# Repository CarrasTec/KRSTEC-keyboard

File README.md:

# KRSTEC-keyboard

These are the KiCad Files for the keyboard that I designed.

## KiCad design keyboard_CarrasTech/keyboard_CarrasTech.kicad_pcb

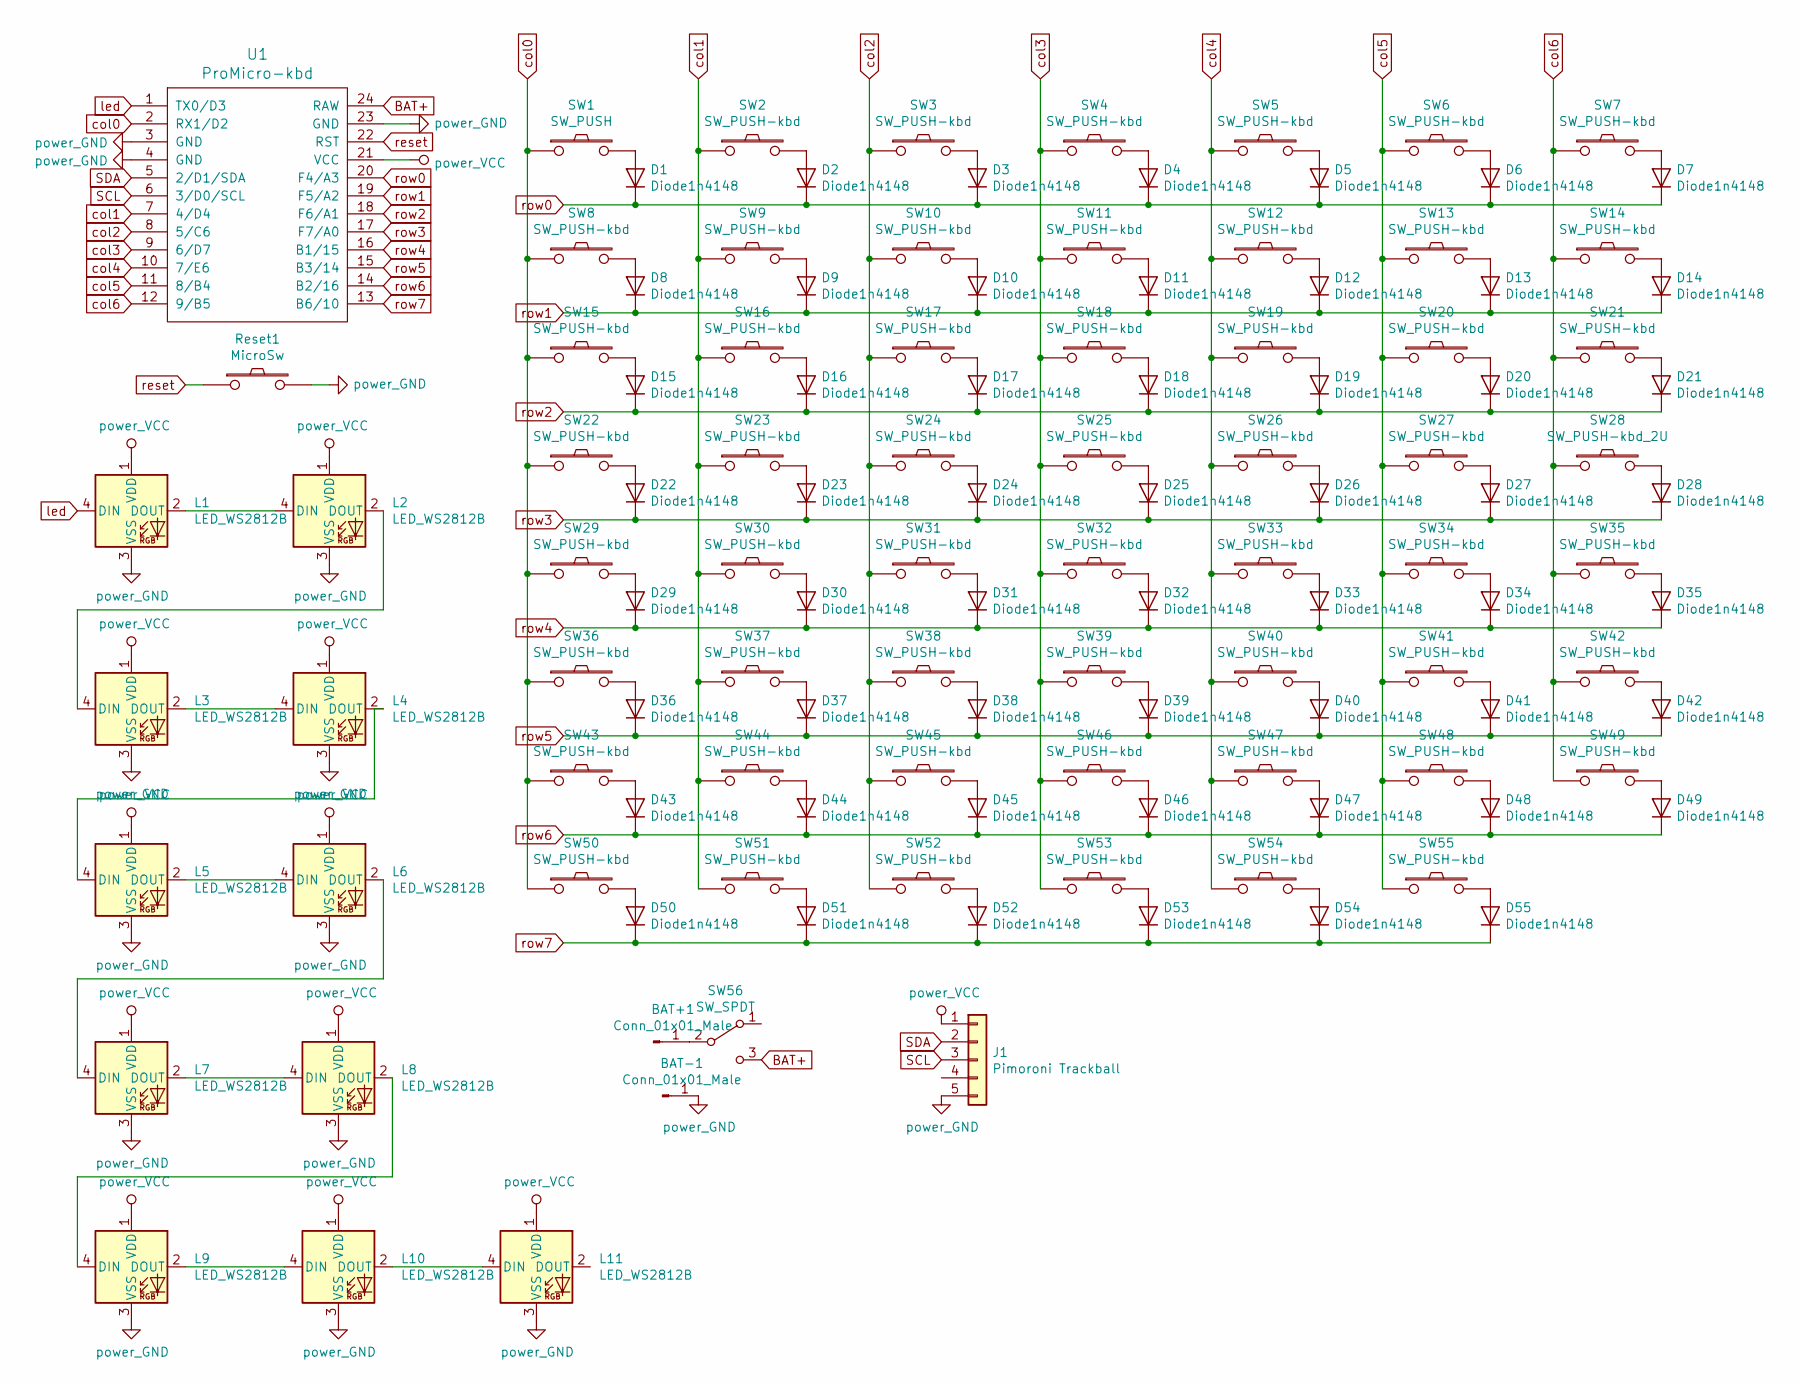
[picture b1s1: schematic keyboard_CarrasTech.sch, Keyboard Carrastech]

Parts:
BAT+1: Conn_01x01_Male; TestPoint_Pad_D2.0mm
BAT-1: Conn_01x01_Male; TestPoint_Pad_D2.0mm
D1, D2, D3, D4, D5, D6, D7, D8, D9, D10, D11, D12, D13, D14, D15, D16, D17, D18, D19, D20, D21, D22, D23, D24, D25, D26, D27, D28, D29, D30, D31, D32, D33, D34, D35, D36, D37, D38, D39, D40, D41, D42, D43, D44, D45, D46, D47, D48, D49, D50, D51, D52, D53, D54, D55: Diode1n4148; D3_SMD_1side
J1: Pimoroni Trackball; PinHeader_1x05_P2.54mm_Vertical
L1, L2, L3, L4, L5, L6, L7, L8, L9, L10, L11: LED_WS2812B; LED_WS2812B_PLCC4_5.0x5.0mm_P3.2mm
Reset1: MicroSw; ResetSW_1side
SW1: SW_PUSH; MXOnly-1U-Hotswap
SW2, SW3, SW4, SW5, SW6, SW7, SW8, SW9, SW10, SW11, SW12, SW13, SW14, SW15, SW16, SW17, SW18, SW19, SW20, SW21, SW22, SW23, SW24, SW25, SW26, SW27, SW29, SW30, SW31, SW32, SW33, SW34, SW35, SW36, SW37, SW38, SW39, SW40, SW41, SW42, SW43, SW44, SW45, SW46, SW47, SW48, SW49, SW50, SW51, SW52, SW53, SW54, SW55: SW_PUSH-kbd; MXOnly-1U-Hotswap
SW28: SW_PUSH-kbd_2U; MXOnly-2U-Hotswap-ReversedStabilizers
SW56: SW_SPDT; SW_SPDT_PCM12
U1: ProMicro-kbd; ProMicro

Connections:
BAT+: SW56.3 (C), U1.24 (RAW)
GND: BAT-1.1, J1.5, L1.3 (VSS), L2.3 (VSS), L3.3 (VSS), L4.3 (VSS), L5.3 (VSS), L6.3 (VSS), L7.3 (VSS), L8.3 (VSS), L9.3 (VSS), L10.3 (VSS), L11.3 (VSS), Reset1.2, U1.3 (GND), U1.4 (GND), U1.23 (GND)
unnamed: BAT+1.1, SW56.2 (B)
unnamed: D1.2 (A), SW1.2
unnamed: D2.2 (A), SW2.2
unnamed: D3.2 (A), SW3.2
unnamed: D4.2 (A), SW4.2
unnamed: D5.2 (A), SW5.2
unnamed: D6.2 (A), SW6.2
unnamed: D7.2 (A), SW7.2
unnamed: D8.2 (A), SW8.2
unnamed: D9.2 (A), SW9.2
unnamed: D10.2 (A), SW10.2
unnamed: D11.2 (A), SW11.2
unnamed: D12.2 (A), SW12.2
unnamed: D13.2 (A), SW13.2
unnamed: D14.2 (A), SW14.2
unnamed: D15.2 (A), SW15.2
unnamed: D16.2 (A), SW16.2
unnamed: D17.2 (A), SW17.2
unnamed: D18.2 (A), SW18.2
unnamed: D19.2 (A), SW19.2
unnamed: D20.2 (A), SW20.2
unnamed: D21.2 (A), SW21.2
unnamed: D22.2 (A), SW22.2
unnamed: D23.2 (A), SW23.2
unnamed: D24.2 (A), SW24.2
unnamed: D25.2 (A), SW25.2
unnamed: D26.2 (A), SW26.2
unnamed: D27.2 (A), SW27.2
unnamed: D28.2 (A), SW28.2
unnamed: D29.2 (A), SW29.2
unnamed: D30.2 (A), SW30.2
unnamed: D31.2 (A), SW31.2
unnamed: D32.2 (A), SW32.2
unnamed: D33.2 (A), SW33.2
unnamed: D34.2 (A), SW34.2
unnamed: D35.2 (A), SW35.2
unnamed: D36.2 (A), SW36.2
unnamed: D37.2 (A), SW37.2
unnamed: D38.2 (A), SW38.2
unnamed: D39.2 (A), SW39.2
unnamed: D40.2 (A), SW40.2
unnamed: D41.2 (A), SW41.2
unnamed: D42.2 (A), SW42.2
unnamed: D43.2 (A), SW43.2
unnamed: D44.2 (A), SW44.2
unnamed: D45.2 (A), SW45.2
unnamed: D46.2 (A), SW46.2
unnamed: D47.2 (A), SW47.2
unnamed: D48.2 (A), SW48.2
unnamed: D49.2 (A), SW49.2
unnamed: D50.2 (A), SW50.2
unnamed: D51.2 (A), SW51.2
unnamed: D52.2 (A), SW52.2
unnamed: D53.2 (A), SW53.2
unnamed: D54.2 (A), SW54.2
unnamed: D55.2 (A), SW55.2
unnamed: L1.2 (DOUT), L2.4 (DIN)
unnamed: L2.2 (DOUT), L3.4 (DIN)
unnamed: L3.2 (DOUT), L4.4 (DIN)
unnamed: L4.2 (DOUT), L5.4 (DIN)
unnamed: L5.2 (DOUT), L6.4 (DIN)
unnamed: L6.2 (DOUT), L7.4 (DIN)
unnamed: L7.2 (DOUT), L8.4 (DIN)
unnamed: L8.2 (DOUT), L9.4 (DIN)
unnamed: L10.2 (DOUT), L11.4 (DIN)
unnamed: L9.2 (DOUT), L10.4 (DIN)
SCL: J1.3, U1.6 (3/D0/SCL)
SDA: J1.2, U1.5 (2/D1/SDA)
VCC: J1.1, L1.1 (VDD), L2.1 (VDD), L3.1 (VDD), L4.1 (VDD), L5.1 (VDD), L6.1 (VDD), L7.1 (VDD), L8.1 (VDD), L9.1 (VDD), L10.1 (VDD), L11.1 (VDD), U1.21 (VCC)
col0: SW1.1, SW8.1, SW15.1, SW22.1, SW29.1, SW36.1, SW43.1, SW50.1, U1.2 (RX1/D2)
col1: SW2.1, SW9.1, SW16.1, SW23.1, SW30.1, SW37.1, SW44.1, SW51.1, U1.7 (4/D4)
col2: SW3.1, SW10.1, SW17.1, SW24.1, SW31.1, SW38.1, SW45.1, SW52.1, U1.8 (5/C6)
col3: SW4.1, SW11.1, SW18.1, SW25.1, SW32.1, SW39.1, SW46.1, SW53.1, U1.9 (6/D7)
col4: SW5.1, SW12.1, SW19.1, SW26.1, SW33.1, SW40.1, SW47.1, SW54.1, U1.10 (7/E6)
col5: SW6.1, SW13.1, SW20.1, SW27.1, SW34.1, SW41.1, SW48.1, SW55.1, U1.11 (8/B4)
col6: SW7.1, SW14.1, SW21.1, SW28.1, SW35.1, SW42.1, SW49.1, U1.12 (9/B5)
led: L1.4 (DIN), U1.1 (TX0/D3)
reset: Reset1.1, U1.22 (RST)
row0: D1.1 (K), D2.1 (K), D3.1 (K), D4.1 (K), D5.1 (K), D6.1 (K), D7.1 (K), U1.20 (F4/A3)
row1: D8.1 (K), D9.1 (K), D10.1 (K), D11.1 (K), D12.1 (K), D13.1 (K), D14.1 (K), U1.19 (F5/A2)
row2: D15.1 (K), D16.1 (K), D17.1 (K), D18.1 (K), D19.1 (K), D20.1 (K), D21.1 (K), U1.18 (F6/A1)
row3: D22.1 (K), D23.1 (K), D24.1 (K), D25.1 (K), D26.1 (K), D27.1 (K), D28.1 (K), U1.17 (F7/A0)
row4: D29.1 (K), D30.1 (K), D31.1 (K), D32.1 (K), D33.1 (K), D34.1 (K), D35.1 (K), U1.16 (B1/15)
row5: D36.1 (K), D37.1 (K), D38.1 (K), D39.1 (K), D40.1 (K), D41.1 (K), D42.1 (K), U1.15 (B3/14)
row6: D43.1 (K), D44.1 (K), D45.1 (K), D46.1 (K), D47.1 (K), D48.1 (K), D49.1 (K), U1.14 (B2/16)
row7: D50.1 (K), D51.1 (K), D52.1 (K), D53.1 (K), D54.1 (K), D55.1 (K), U1.13 (B6/10)

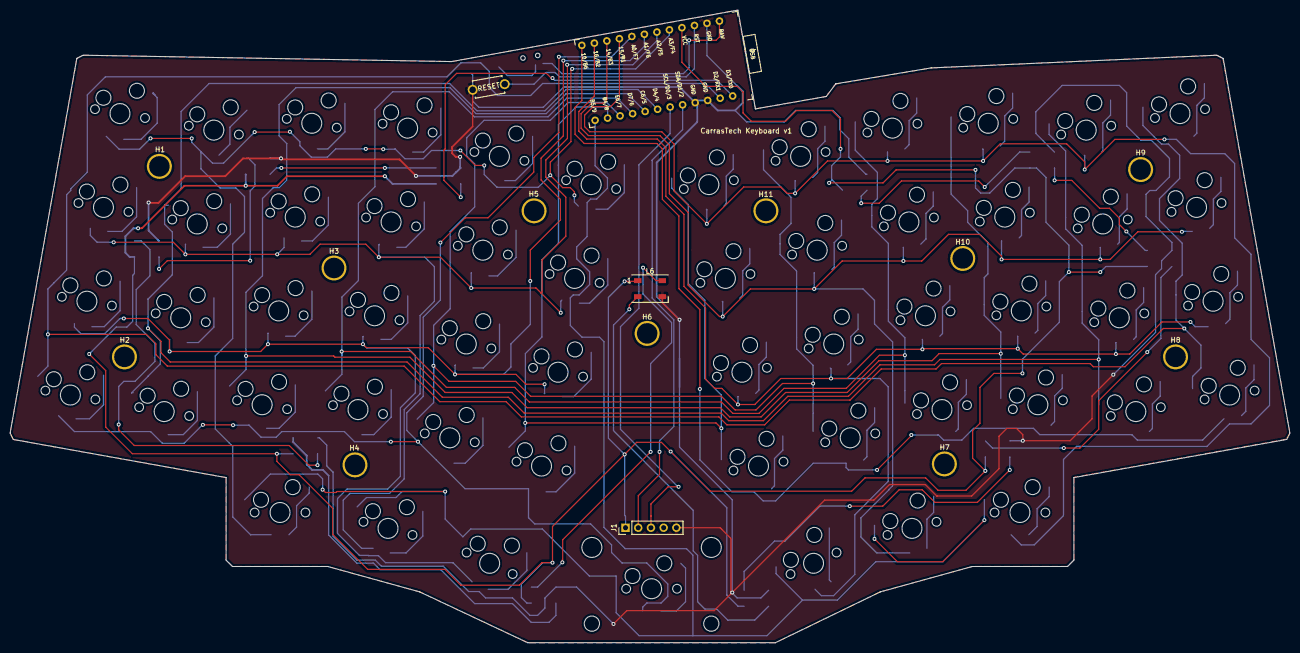
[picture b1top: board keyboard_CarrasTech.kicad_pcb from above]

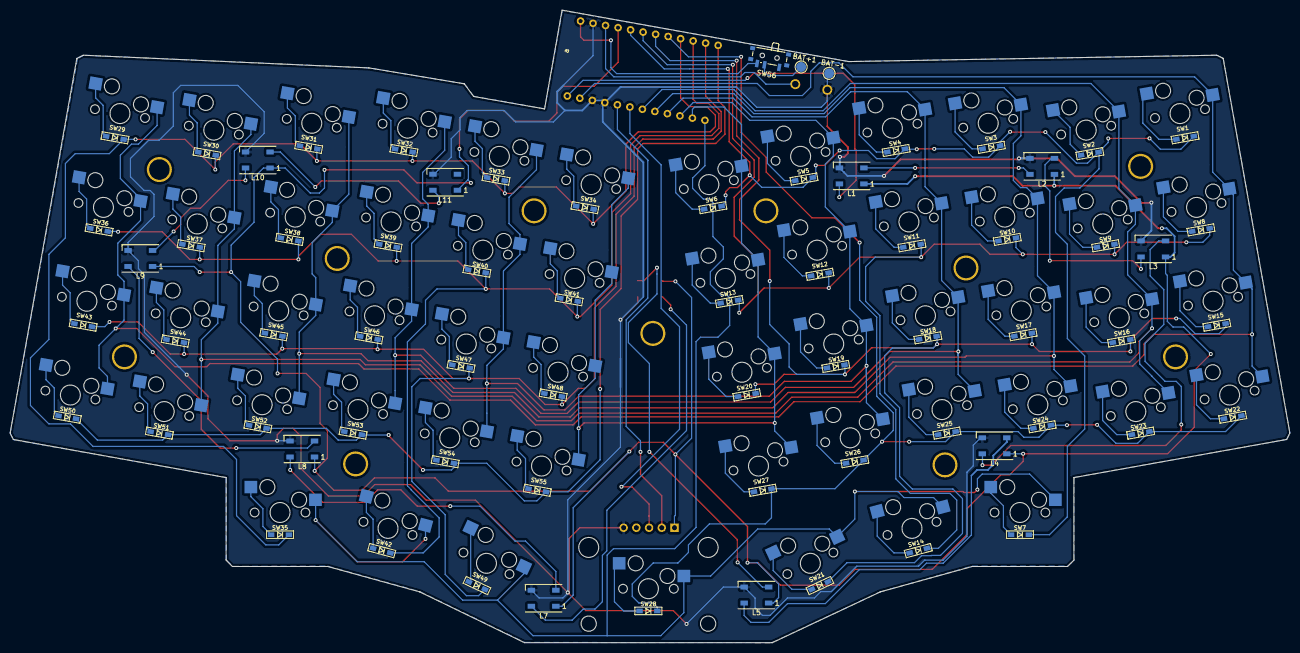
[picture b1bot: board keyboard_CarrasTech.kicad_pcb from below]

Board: 2 copper layers, 255.9 x 126.5 mm, 138 parts (68 on the bottom side), 88 nets.

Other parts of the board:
H1: H1; MountingHole_4mm
H2: H2; MountingHole_4mm
H3: H3; MountingHole_4mm
H4: H4; MountingHole_4mm
H5: H5; MountingHole_4mm
H6: H6; MountingHole_4mm
H7: H7; MountingHole_4mm
H8: H8; MountingHole_4mm
H9: H9; MountingHole_4mm
H10: H10; MountingHole_4mm
H11: H11; MountingHole_4mm

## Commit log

2022-10-18 Add files via upload
    Initial Commit
2022-10-18 Create README.md
    Initial Commit
